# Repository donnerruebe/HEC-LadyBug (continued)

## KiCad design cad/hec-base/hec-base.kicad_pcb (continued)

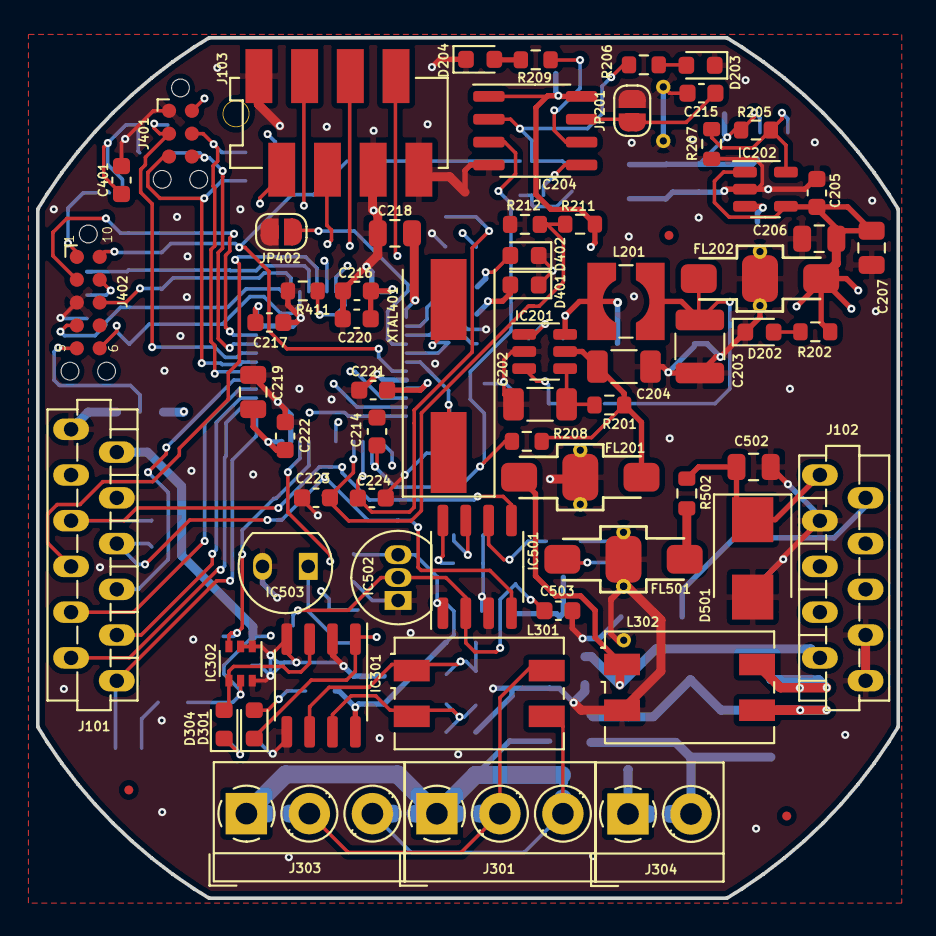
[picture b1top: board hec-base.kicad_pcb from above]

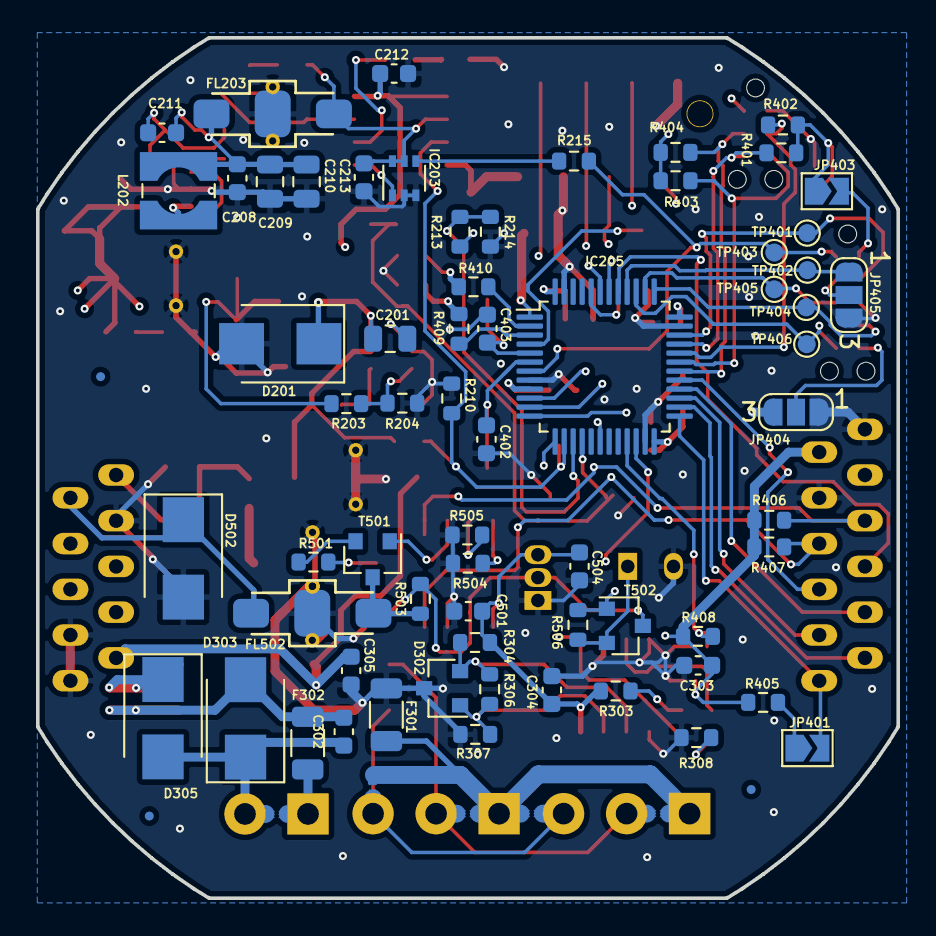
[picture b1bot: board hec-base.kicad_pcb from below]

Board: 4 copper layers, 47.8 x 47.8 mm, 140 parts (73 on the bottom side), 82 nets.

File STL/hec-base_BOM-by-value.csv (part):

"Source:","/home/lode/MT_workspace/Marienkaefer/cad/hec-base/hec-base.sch"
"Date:","So 14 Aug 2022 20:23:33 CEST"
"Tool:","Eeschema 5.1.12"
"Generator:","/usr/share/kicad/plugins/bom_csv_grouped_by_value_with_fp.py"
"Component Count:","145"
"Ref","Qnty","Value","Cmp name","Footprint","Description","Vendor"
"C201, ","1","1uF 50V","C","Capacitor_SMD:C_0805_2012Metric","Unpolarized capacitor",""
"C202, C204, ","2","10uF 50V","C","Capacitor_SMD:C_1206_3216Metric","Unpolarized capacitor",""
"C203, ","1","47uF 10V","C","Capacitor_SMD:C_1210_3225Metric","Unpolarized capacitor",""
"C205, C208, C211, C212, C213, C214, C215, C216, C217, C220, C221, C222, C223, C224, C302, C303, C304, C305, C401, C501, C504, ","21","100nF","C","Capacitor_SMD:C_0603_1608Metric","Unpolarized capacitor",""
"C206, C207, C209, C210, C218, C219, ","6","4.7uF 10V","C","Capacitor_SMD:C_0805_2012Metric","Unpolarized capacitor",""
"C301, ","1","1uF","C","","Unpolarized capacitor",""
"C402, C403, ","2","15pF","C","Capacitor_SMD:C_0603_1608Metric","Unpolarized capacitor",""
"C502, ","1","10uF","C","Capacitor_SMD:C_0805_2012Metric","Unpolarized capacitor",""
"C503, ","1","10nF","C","Capacitor_SMD:C_0603_1608Metric","Unpolarized capacitor",""
"D201, D303, ","2","MBRS140","D","Diode_SMD:D_SMB","Diode",""
"D202, D203, D204, D301, D304, ","5","LED","LED_Small","LED_SMD:LED_0603_1608Metric","Light emitting diode, small symbol",""
"D302, ","1","WE 824022","D_TVS_Dual_AAC","Package_TO_SOT_SMD:SOT-23","Bidirectional dual transient-voltage-suppression diode, center on pin 3",""
"D305, ","1","P6SMB30CA","D_TVS","Diode_SMD:D_SMB","Bidirectional transient-voltage-suppression diode",""
"D401, ","1","LED rot","LED_Small","LED_SMD:LED_0603_1608Metric","Light emitting diode, small symbol",""
"D402, ","1","LED gruen","LED_Small","LED_SMD:LED_0603_1608Metric","Light emitting diode, small symbol",""
"D501, D502, ","2","P6SM6A","D_Zener_Small","Diode_SMD:D_SMB","Zener diode, small symbol",""
"E301, E302, E303, E304, E305, ","5","SPARK_GAP","SparkGap","SparkGaps_MT:SparkGap_3pin_0.67x0.5mm","Spark gap",""
"F301, F302, ","2","ESKA BSMD1206-SS0.5","Fuse_Small","Resistor_SMD:R_1206_3216Metric","Fuse, small symbol",""
"FID101, FID102, FID103, FID104, FID105, FID106, ","6","Fiducial","Fiducial","Fiducial:Fiducial_0.5mm_Mask1mm","Fiducial Marker",""
"FL201, FL202, FL203, FL501, FL502, ","5","NFE61P681B1H9L","Filter_EMI_LCL","Filter_MT:Murata_NFE61P","EMI T-filter (LCL)",""
"IC201, ","1","LMR14206","LMR14206","Package_TO_SOT_SMD:SOT-23-6","Simple Switcher Buck Regulator, Vin=4.5-42V, Iout=600mA, Adjustable output voltage, SOT-23-6 package",""
"IC202, ","1","LTC3406ES5","LTC3406ES5","Package_TO_SOT_SMD:TSOT-23-5","600mA Synchronous Step-Down Regulator, 1.5MHz, Adjustable Output Voltage, Burst Mode, ThinSOT-23",""
"IC203, IC302, ","2","74LVC1G57","74LVC1G57","Package_TO_SOT_SMD:SOT-363_SC-70-6","Configurable Multi-Function Single Gate, Low-Voltage CMOS",""
"IC204, ","1","TPS3307-33","TPS3307-33","Package_SO:SO-8_3.9x4.9mm_P1.27mm","",""
"IC205, ","1","STM32F103C8Tx","STM32F103C8Tx","Package_QFP:LQFP-48_7x7mm_P0.5mm","ARM Cortex-M3 MCU, 64KB flash, 20KB RAM, 72MHz, 2-3.6V, 37 GPIO, LQFP-48",""
"IC301, ","1","MAX485E","MAX485E","Package_SO:SO-8_3.9x4.9mm_P1.27mm","Half duplex RS-485/RS-422, 2.5 Mbps, ±15kV electro-static discharge (ESD) protection, no slew-rate, no low-power shutdown, with receiver/driver enable, 32 receiver drive kapacitity, DIP-8 and SOIC-8",""
"IC501, ","1","DS2482S-100","DS2482S-100","Package_SO:SO-8_3.9x4.9mm_P1.27mm","",""
"IC502, ","1","DS18B20","DS18B20","Package_TO_SOT_THT:TO-92_Inline","Programmable Resolution 1-Wire Digital Thermometer TO-92",""
"IC503, ","1","DS28E25","DS28E25","Package_TO_SOT_THT:TO-92-2","",""
"J101, ","1","Micromatch 12p","Conn_01x12","Connectors_MicroMatch_MT:ConnectorMicromatch-12-horizontal-THT","Generic connector, single row, 01x12, script generated (kicad-library-utils/schlib/autogen/connector/)",""
"J102, ","1","Micromatch 10p","Conn_01x10","Connectors_MicroMatch_MT:ConnectorMicromatch-10-horizontal-THT","Generic connector, single row, 01x10, script generated (kicad-library-utils/schlib/autogen/connector/)",""
"J103, ","1","Micromatch 8p","Conn_01x08","Connectors_MicroMatch_MT:ConnectorMicromatch-8-SMD-polarized","Generic connector, single row, 01x08, script generated (kicad-library-utils/schlib/autogen/connector/)",""
"J301, J303, ","2","AKL-166-03","Screw_Terminal_01x03","TerminalBlock_MetzConnect:TerminalBlock_MetzConnect_Type059_RT06303HBWC_1x03_P3.50mm_Horizontal","Generic screw terminal, single row, 01x03, script generated (kicad-library-utils/schlib/autogen/connector/)",""
"J302, ","1","Conn_01x03_Male","Conn_01x03_Male","","Generic connector, single row, 01x03, script generated (kicad-library-utils/schlib/autogen/connector/)",""
"J304, ","1","AKL-166-02","Screw_Terminal_01x02","TerminalBlock_MetzConnect:TerminalBlock_MetzConnect_Type059_RT06302HBWC_1x02_P3.50mm_Horizontal","Generic screw terminal, single row, 01x02, script generated (kicad-library-utils/schlib/autogen/connector/)",""
"J401, ","1","Tag-Connect 2x3","TC2030-IDC-console","Tag-Connect:Tag-Connect_TC2030-IDC-NL_2x03_P1.27mm_Vertical","Header, Tagconnect, 2x3, console-adapter",""
"J402, ","1","Tag-Connect 2x5","Conn_02x05_Odd_Even","Tag-Connect:Tag-Connect_TC2050-IDC-NL_2x05_P1.27mm_Vertical","Generic connector, double row, 02x05, odd/even pin numbering scheme (row 1 odd numbers, row 2 even numbers), script generated (kicad-library-utils/schlib/autogen/connector/)",""
"JP201, JP402, ","2","SolderJumper_2_Open","SolderJumper_2_Open","Jumper:SolderJumper-2_P1.3mm_Open_RoundedPad1.0x1.5mm","Solder Jumper, 2-pole, open",""
"JP401, JP403, ","2","SolderJumper_2_Open","SolderJumper_2_Open","Jumper:SolderJumper-2_P1.3mm_Open_TrianglePad1.0x1.5mm","Solder Jumper, 2-pole, open",""
"JP404, JP405, ","2","SolderJumper_3_Open","SolderJumper_3_Open","Jumper:SolderJumper-3_P1.3mm_Open_RoundedPad1.0x1.5mm_NumberLabels","Solder Jumper, 3-pole, open",""
"L201, ","1","15uH, 1A WE 744053150","L_Ferrite","Inductor_SMD:L_Wuerth_WE-TPC-3816","Inductor with ferrite core",""
"L202, ","1","2,5uH, 1,25A, 0R05 WE 744031002","L_Ferrite","Inductor_SMD:L_Wuerth_WE-TPC-3816","Inductor with ferrite core",""
"L301, ","1","WE 744227","L_Ferrite_Coupled_1423","Inductor_SMD:L_CommonMode_Wuerth_WE-SL2","Coupled inductor with ferrite core",""
"L302, ","1","WE 744220","L_Ferrite_Coupled_1423","Inductor_SMD:L_CommonMode_Wuerth_WE-SL2","Coupled inductor with ferrite core",""
"R201, ","1","301k","R","Resistor_SMD:R_0603_1608Metric","Resistor",""
"R202, R209, R303, R308, ","4","330R","R","Resistor_SMD:R_0603_1608Metric","Resistor",""
"R203, ","1","5k62 1%","R","Resistor_SMD:R_0603_1608Metric","Resistor",""
"R204, ","1","1k02 1%","R","Resistor_SMD:R_0603_1608Metric","Resistor",""
"R205, ","1","301k 1%","R","Resistor_SMD:R_0603_1608Metric","Resistor",""
"R206, R215, R409, R410, ","4","120R","R","Resistor_SMD:R_0603_1608Metric","Resistor",""
"R207, R208, ","2","66k5 1%","R","Resistor_SMD:R_0603_1608Metric","Resistor",""
"R210, R211, R213, ","3","10k 1%","R","Resistor_SMD:R_0603_1608Metric","Resistor",""
"R212, ","1","2k4 1%","R","Resistor_SMD:R_0603_1608Metric","Resistor",""
"R214, ","1","4k7 1%","R","Resistor_SMD:R_0603_1608Metric","Resistor",""
"R301, R302, R305, ","3","360","R","","Resistor",""
"R304, R307, ","2","2k4","R","Resistor_SMD:R_0603_1608Metric","Resistor",""
"R306, R401, R402, R403, R404, R405, R408, R411, ","8","4k7","R","Resistor_SMD:R_0603_1608Metric","Resistor",""
"R406, R407, R506, ","3","1k","R","Resistor_SMD:R_0603_1608Metric","Resistor",""
"R501, R502, R503, R504, R505, ","5","22R","R","Resistor_SMD:R_0603_1608Metric","Resistor",""
"T501, ","1","BSS84","BSS84","Package_TO_SOT_SMD:SOT-23","-0.13A Id, -50V Vds, P-Channel MOSFET, SOT-23",""
"T502, ","1","BSS123","BSS123","Package_TO_SOT_SMD:SOT-23","0.17A Id, 100V Vds, N-Channel MOSFET, SOT-23",""
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
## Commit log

2020-12-29 Initial project directory layout, first schematic steps.
2020-12-29 Power-Management schematics input and dimensioning done.
2020-12-30 MCU-, Crypto- und One-Wire-Teil erstellt und dimensioniert, ERC bestanden, SLP geplottet, Footprints nur teilweise zugewiesen.
2021-01-02 MCU-, Crypto- und One-Wire-Teil dimensioniert, ERC bestanden, SLP geplottet.
2021-01-07 MT-Marienkaefer: Footprints fertig zugewiesen.
2022-08-14 Entflochtene Leiterplatte mit Schaltplan speichern.
2022-08-14 MT-Marienkaefer: Schaltregler von Platinenkante verschoben.
2022-08-14 Alle in-akzeptablen DRC-Fehler im Layout behoben.
2022-08-14 Texte für Silkscreen und Bestückungsplan platziert.
2022-08-14 Gerberdaten erstellt.
2022-08-14 BOM's erstellt.
